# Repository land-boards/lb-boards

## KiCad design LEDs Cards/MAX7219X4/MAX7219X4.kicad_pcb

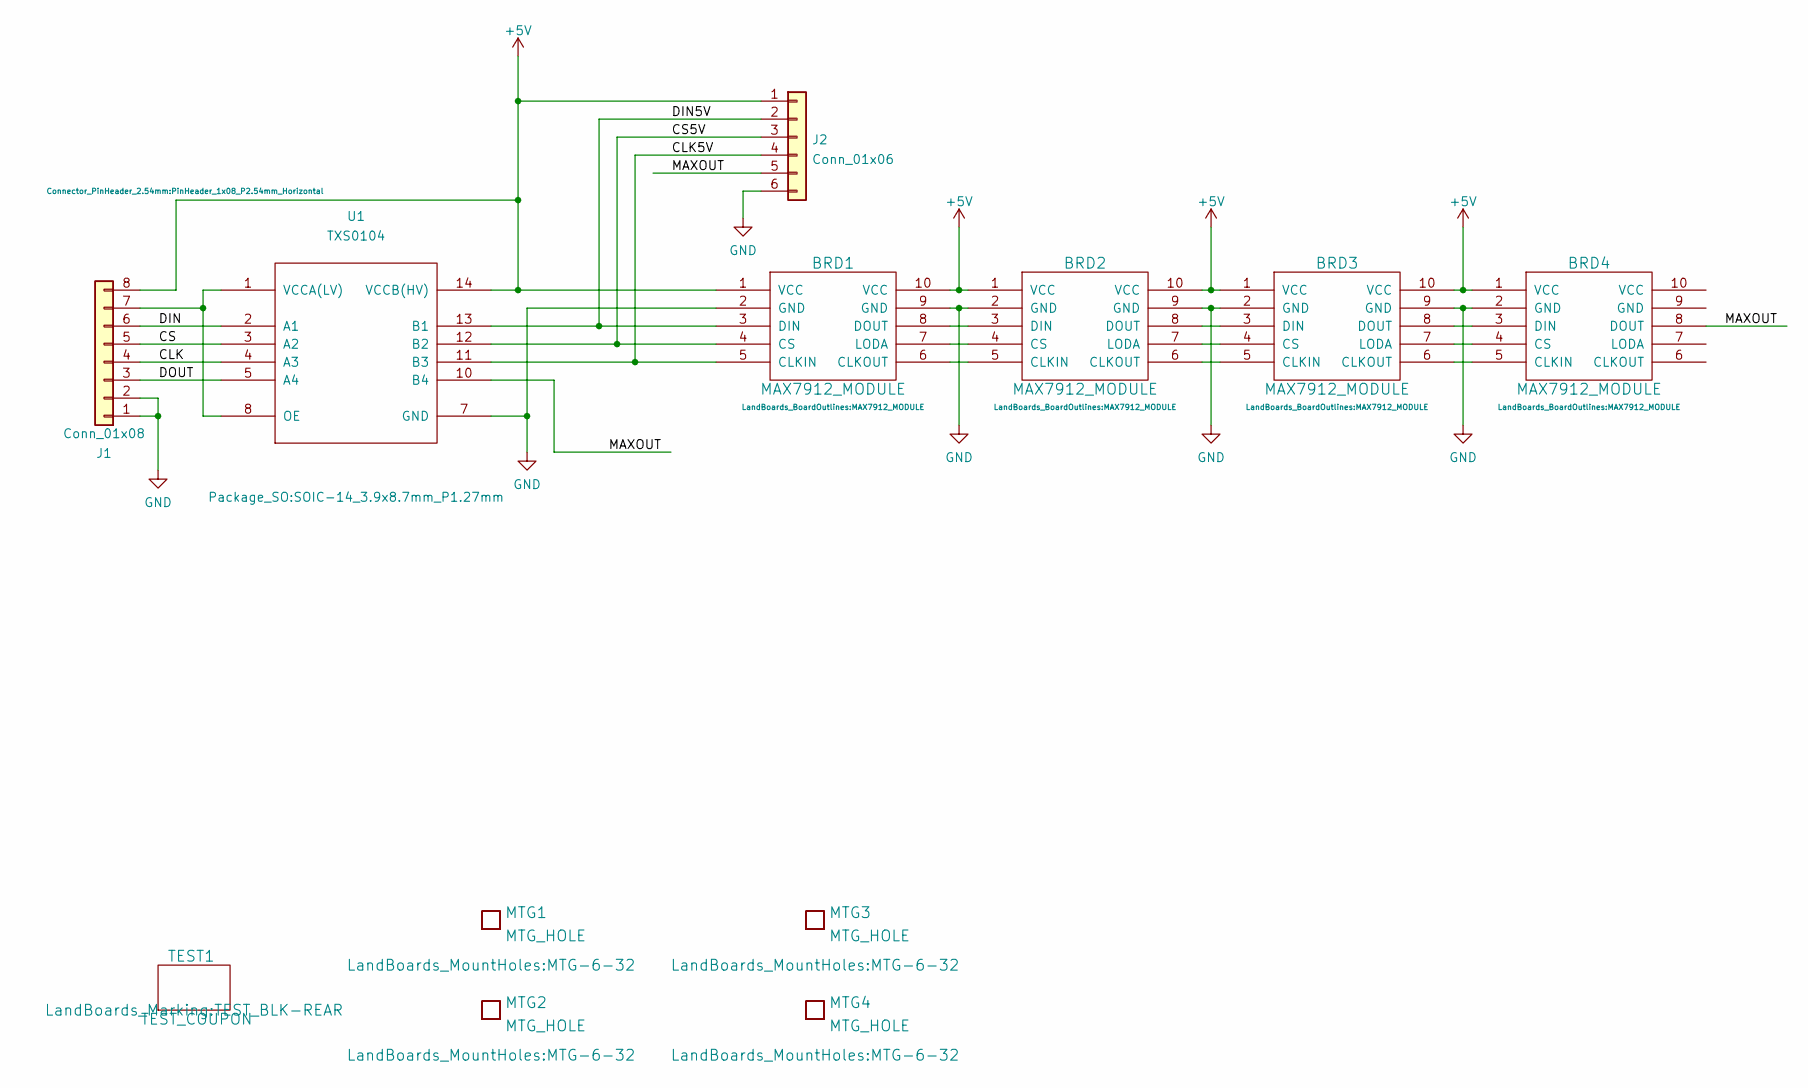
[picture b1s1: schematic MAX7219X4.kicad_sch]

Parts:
BRD1, BRD2, BRD3, BRD4: MAX7912_MODULE
J1: Conn_01x08; PinHeader_1x08_P2.54mm_Horizontal
J2: Conn_01x06; PinHeader_1x06_P2.54mm_Horizontal
MTG1, MTG2, MTG3, MTG4: MTG_HOLE; MTG-6-32
TEST1: TEST_COUPON; TEST_BLK-REAR
U1: TXS0104; SOIC-14_3.9x8.7mm_P1.27mm

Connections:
+5V: BRD1.1 (VCC), BRD1.10 (VCC), BRD2.1 (VCC), BRD2.10 (VCC), BRD3.1 (VCC), BRD3.10 (VCC), BRD4.1 (VCC), J1.8, J2.1, U1.14 (VCCB(HV))
/CLK: J1.4, U1.4 (A3)
/CLK5V: BRD1.5 (CLKIN), J2.4, U1.11 (B3)
/CS: J1.5, U1.3 (A2)
/CS5V: BRD1.4 (CS), J2.3, U1.12 (B2)
/DIN: J1.6, U1.2 (A1)
/DIN5V: BRD1.3 (DIN), J2.2, U1.13 (B1)
/DOUT: J1.3, U1.5 (A4)
/MAXOUT: BRD4.8 (DOUT), J2.5, U1.10 (B4)
GND: BRD1.2 (GND), BRD1.9 (GND), BRD2.2 (GND), BRD2.9 (GND), BRD3.2 (GND), BRD3.9 (GND), BRD4.2 (GND), J1.1, J1.2, J2.6, U1.7 (GND)
unnamed: BRD1.6 (CLKOUT), BRD2.5 (CLKIN)
unnamed: BRD1.7 (LODA), BRD2.4 (CS)
unnamed: BRD1.8 (DOUT), BRD2.3 (DIN)
unnamed: BRD2.6 (CLKOUT), BRD3.5 (CLKIN)
unnamed: BRD2.7 (LODA), BRD3.4 (CS)
unnamed: BRD2.8 (DOUT), BRD3.3 (DIN)
unnamed: BRD3.6 (CLKOUT), BRD4.5 (CLKIN)
unnamed: BRD3.7 (LODA), BRD4.4 (CS)
unnamed: BRD3.8 (DOUT), BRD4.3 (DIN)
unnamed: J1.7, U1.1 (VCCA(LV)), U1.8 (OE)

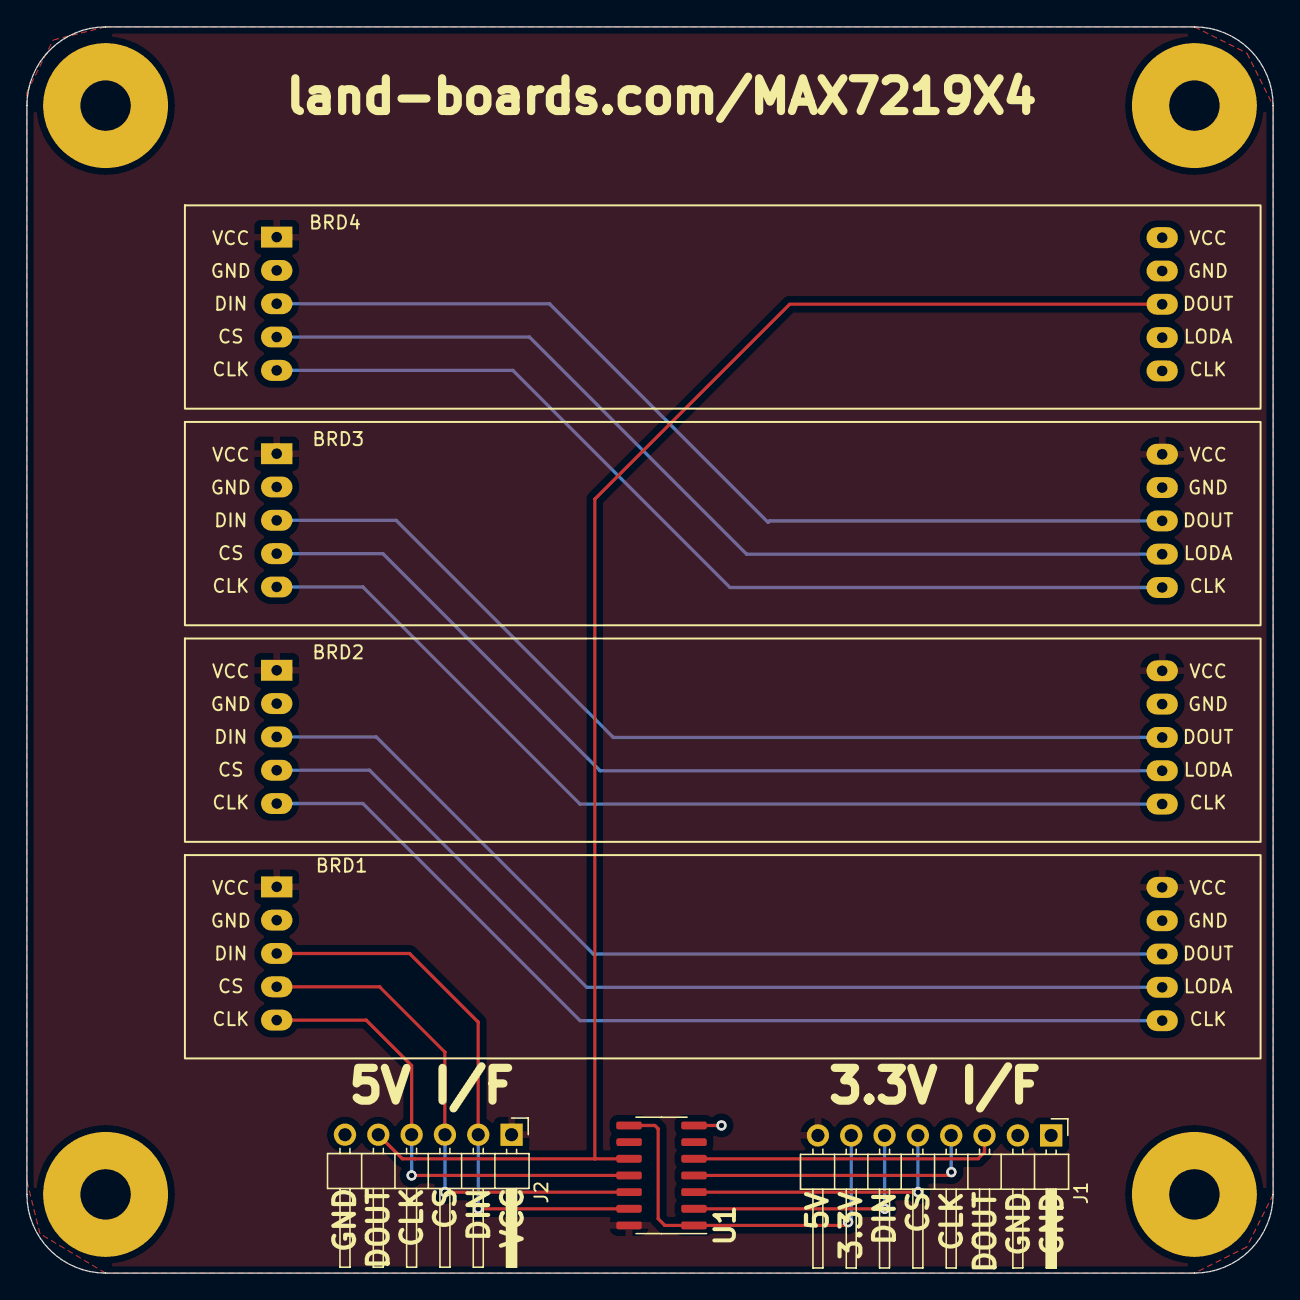
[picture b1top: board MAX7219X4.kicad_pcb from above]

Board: 2 copper layers, 95.0 x 95.0 mm, 12 parts (0 on the bottom side), 20 nets.

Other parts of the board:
TEST: TEST_COUPON; TEST_BLK-REAR

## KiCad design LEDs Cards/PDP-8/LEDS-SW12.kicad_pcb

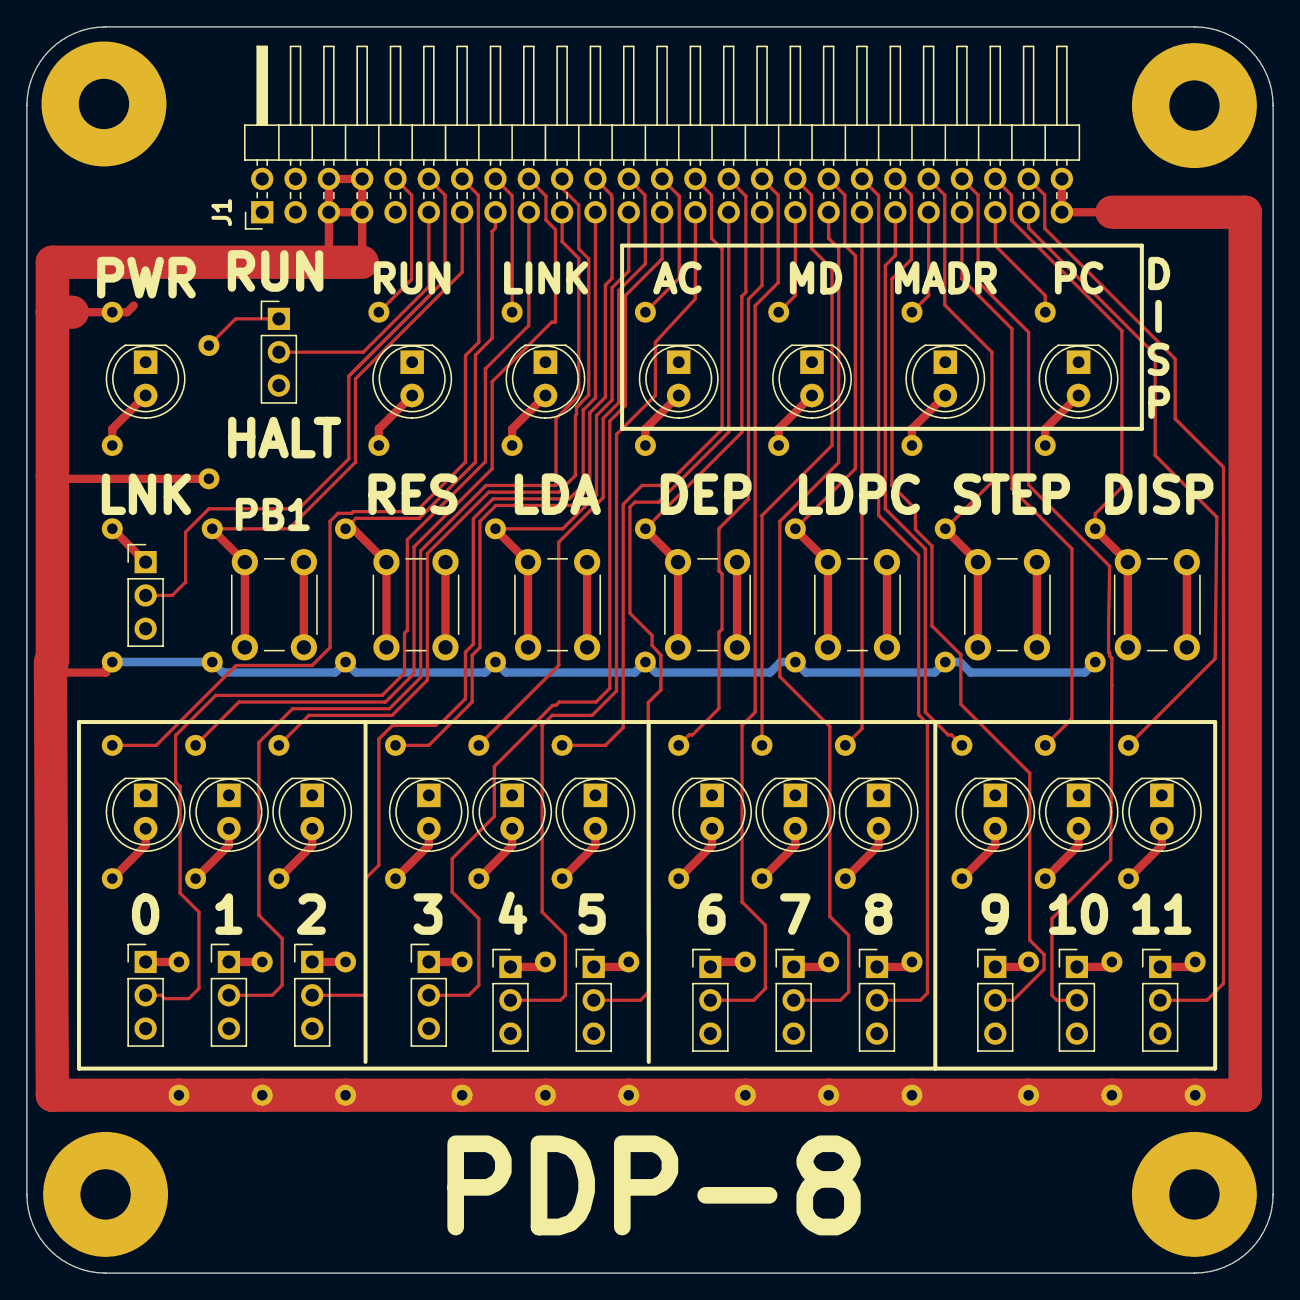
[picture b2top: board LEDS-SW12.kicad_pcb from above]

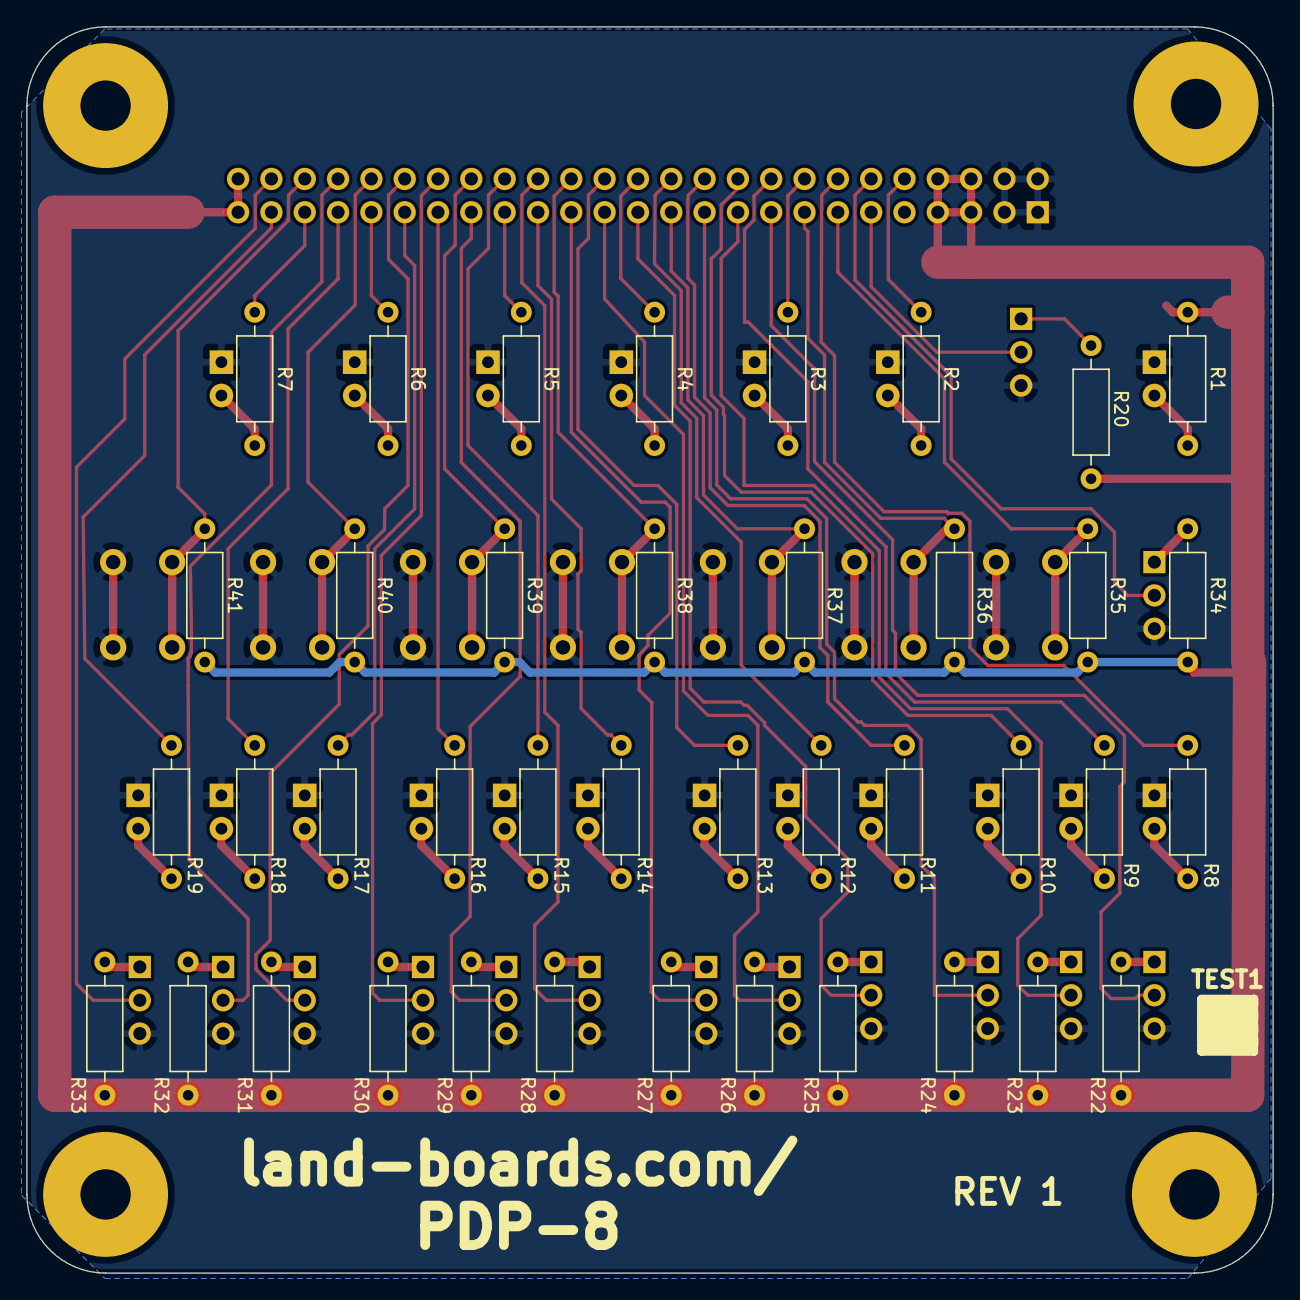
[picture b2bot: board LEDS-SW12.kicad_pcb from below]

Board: 2 copper layers, 95.0 x 95.0 mm, 86 parts (40 on the bottom side), 74 nets.

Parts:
D1, D2, D3, D4, D5, D6, D7, D8, D9, D10, D11, D12, D13, D14, D15, D16, D17, D18, D19: LED-fixed; LED_D5.0mm
J1: Conn_02x25_Odd_Even; PinHeader_2x25_P2.54mm_Horizontal
MTG1, MTG2, MTG3: MTG_HOLE; MTG-6-32
MTG?1: MTG_HOLE; MTG-6-32
R1, R2, R3, R4, R5, R6, R7, R8, R9, R10, R11, R12, R13, R14, R15, R16, R17, R18, R19: 560; R_Axial_DIN0207_L6.3mm_D2.5mm_P10.16mm_Horizontal
R20, R22, R23, R24, R25, R26, R27, R28, R29, R30, R31, R32, R33, R34, R35, R36, R37, R38, R39, R40, R41: 10K; R_Axial_DIN0207_L6.3mm_D2.5mm_P10.16mm_Horizontal
SW1, SW2, SW3, SW4, SW5, SW6, SW7, SW8, SW9, SW10, SW11, SW12, SW13, SW14: SW_SPDT; PinHeader_1x03_P2.54mm_Vertical
SW15, SW16, SW17, SW18, SW19, SW20, SW21: SW_Push; SW_PUSH_6mm_H8.5mm
TEST1: COUPON; TEST_BLK-REAR

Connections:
+5V: J1.5, J1.6, J1.7, J1.8, J1.49, J1.50, R1.2, R20.1, R22.1, R23.1, R24.1, R25.1, R26.1, R27.1, R28.1, R29.1, R30.1, R31.1, R32.1, R33.1, R34.1, R35.1, R36.1, R37.1, R38.1, R39.1, R40.1, R41.1
/DEPOSIT: J1.30, R38.2, SW18.2
/DISP: J1.46, R41.2, SW21.2
/DISPACC: J1.26, R4.2
/DISPMADR: J1.41, R6.2
/DISPMBUF: J1.33, R5.2
/DISPPC: J1.45, R7.2
/DS0: J1.14, R8.2
/DS1: J1.18, R9.2
/DS2: J1.20, R10.2
/DS3: J1.22, R11.2
/DS4: J1.24, R12.2
/DS5: J1.28, R13.2
/DS6: J1.31, R14.2
/DS7: J1.34, R15.2
/DS8: J1.37, R16.2
/DS9: J1.39, R17.2
/DS10: J1.43, R18.2
/DS11: J1.47, R19.2
/LDPC: J1.36, R39.2, SW19.2
/LINK: J1.12, SW2.2
/LINKLED: J1.16, R3.2
/LOADACC: J1.23, R37.2, SW17.2
/PB1: J1.13, R35.2, SW15.2
/RESET: J1.15, R36.2, SW16.2
/RUN: J1.11, SW1.2
/RUNLED: J1.10, R2.2
/SS0: J1.17, SW3.2
/SS1: J1.19, SW4.2
/SS2: J1.21, SW5.2
/SS3: J1.25, SW6.2
/SS4: J1.27, SW7.2
/SS5: J1.29, SW8.2
/SS6: J1.32, SW9.2
/SS7: J1.35, SW10.2
/SS8: J1.38, SW11.2
/SS9: J1.40, SW12.2
/SS10: J1.44, SW13.2
/SS11: J1.48, SW14.2
/STEP: J1.42, R40.2, SW20.2
GND: D1.1, D2.1, D3.1, D4.1, D5.1, D6.1, D7.1, D8.1, D9.1, D10.1, D11.1, D12.1, D13.1, D14.1, D15.1, D16.1, D17.1, D18.1, D19.1, J1.1, J1.2, J1.3, J1.4, SW1.3, SW2.3, SW3.3, SW4.3, SW5.3, SW6.3, SW7.3, SW8.3, SW9.3, SW10.3, SW11.3, SW12.3, SW13.3, SW14.3, SW15.1, SW16.1, SW17.1, SW18.1, SW19.1, SW20.1, SW21.1
unnamed: D1.2, R1.1
unnamed: D2.2, R2.1
unnamed: D3.2, R3.1
unnamed: D4.2, R4.1
unnamed: D5.2, R5.1
unnamed: D6.2, R6.1
unnamed: D7.2, R7.1
unnamed: D8.2, R8.1
unnamed: D9.2, R9.1
unnamed: D10.2, R10.1
unnamed: D11.2, R11.1
unnamed: D12.2, R12.1
unnamed: D13.2, R13.1
unnamed: D14.2, R14.1
unnamed: D15.2, R15.1
unnamed: D16.2, R16.1
unnamed: D17.2, R17.1
unnamed: D18.2, R18.1
unnamed: D19.2, R19.1
unnamed: R20.2, SW1.1
unnamed: R22.2, SW3.1
unnamed: R23.2, SW4.1
unnamed: R24.2, SW5.1
unnamed: R25.2, SW6.1
unnamed: R26.2, SW7.1
unnamed: R27.2, SW8.1
unnamed: R28.2, SW9.1
unnamed: R29.2, SW10.1
unnamed: R30.2, SW11.1
unnamed: R31.2, SW12.1
unnamed: R32.2, SW13.1
unnamed: R33.2, SW14.1
unnamed: R34.2, SW2.1

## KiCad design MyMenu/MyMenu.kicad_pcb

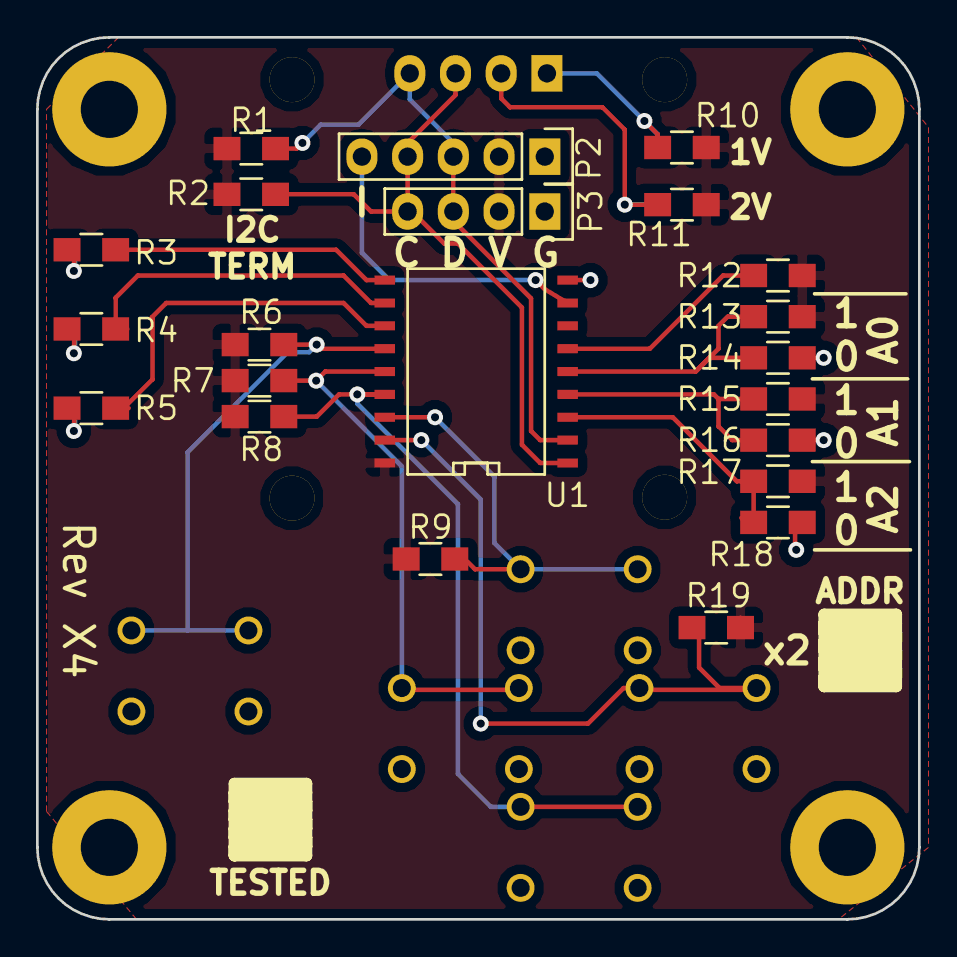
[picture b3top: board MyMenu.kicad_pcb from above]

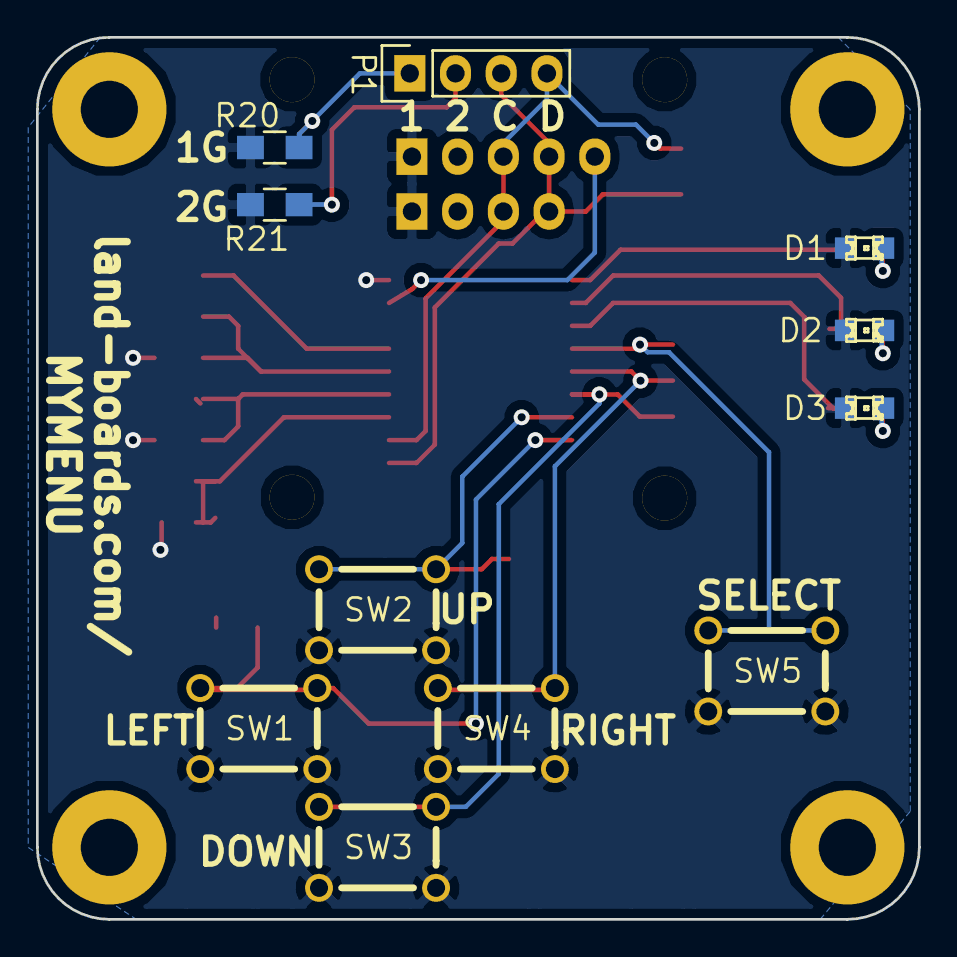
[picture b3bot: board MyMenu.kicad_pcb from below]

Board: 2 copper layers, 49.0 x 49.0 mm, 43 parts (13 on the bottom side), 22 nets.

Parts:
ADDR: VAL**; TEST_BLK-REAR
D1, D2, D3: LED; LED-0805
MTG1, MTG2, MTG3, MTG4: CONN_1; MTG-4-40
MTG5, MTG6, MTG7, MTG8: CONN_1; MTG-2.5MM
P1, P3: CONN_4; Pin_Header_Straight_1x04
P2: CONN_5; Pin_Header_Straight_1x05
R1, R2: 2.2K; R_0805_HandSoldering
R3, R4, R5: 330; R_0805_HandSoldering
R6, R7, R8, R9, R12, R19: 10K; R_0805_HandSoldering
R10, R11, R20, R21: 0/OP; R_0805_HandSoldering
R13, R15, R17: OPEN; R_0805_HandSoldering
R14, R16, R18: 0; R_0805_HandSoldering
SW1, SW2, SW3, SW4, SW5: SW_PUSH_OMRON; SW-PB-6MM
TESTED: VAL**; TEST_BLK-REAR
U1: MCP23008SO; SO18W

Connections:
/A0: R13.2, R14.1, U1.5
/A1: R15.2, R16.1, U1.4
/A2: R17.2, R18.1, U1.3
/GND: D1.2, D2.2, D3.2, P2.1, P3.1, R14.2, R16.2, R18.2, R20.2, R21.2, SW1.3, SW1.4, SW2.3, SW2.4, SW3.3, SW3.4, SW4.3, SW4.4, SW5.3, SW5.4, U1.9
/SCL: P1.3, P2.4, P3.4, R2.2, U1.1
/SDA: P1.4, P2.3, P3.3, R1.2, U1.2
/VCC: P2.2, P3.2, R1.1, R2.1, R6.1, R7.1, R8.1, R9.1, R10.1, R11.1, R12.1, R13.1, R15.1, R17.1, R19.1, U1.18
unnamed: D1.1, R3.2
unnamed: D2.1, R4.2
unnamed: D3.1, R5.2
unnamed: P1.1, R10.2, R20.1
unnamed: P1.2, R11.2, R21.1
unnamed: P2.5, U1.8
unnamed: R3.1, U1.10
unnamed: R4.1, U1.11
unnamed: R5.1, U1.12
unnamed: R6.2, SW5.1, SW5.2, U1.13
unnamed: R7.2, SW4.1, SW4.2, U1.14
unnamed: R8.2, SW3.1, SW3.2, U1.15
unnamed: R9.2, SW2.1, SW2.2, U1.16
unnamed: R12.2, U1.6
unnamed: R19.2, SW1.1, SW1.2, U1.17

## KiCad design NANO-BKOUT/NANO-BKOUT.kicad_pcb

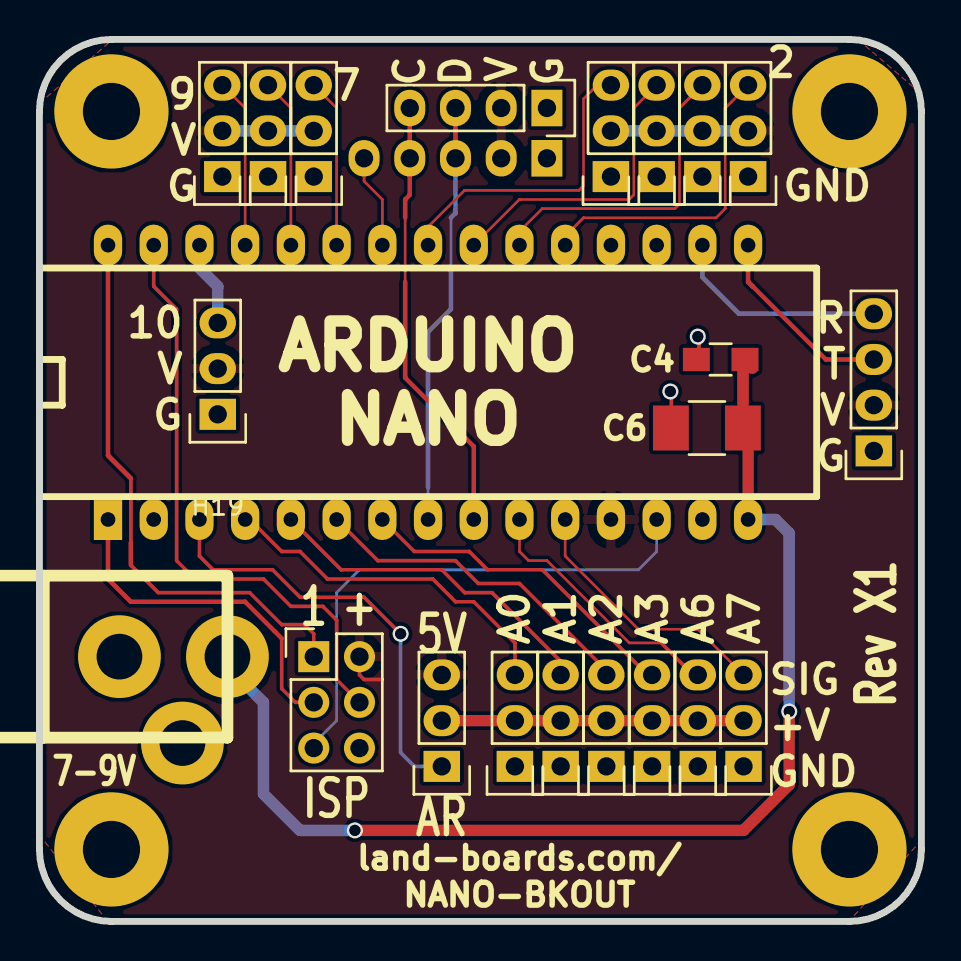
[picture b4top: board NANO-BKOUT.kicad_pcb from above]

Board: 2 copper layers, 49.0 x 49.0 mm, 27 parts (1 on the bottom side), 28 nets.

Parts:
C4: 0.1uF; R_0805_HandSoldering
C6: 22uF; R_1210_HandSoldering
H1, H2, H3, H4, H5, H6, H9, H10, H11, H12, H14, H15, H16, H18, H19: CONN_01X03; Pin_Header_Straight_1x03
H7: CONN_01X05; Pin_Header_Straight_1x05
H8: CONN_02X03; Pin_Header_Straight_2x03
H13, H17: CONN_01X04; Pin_Header_Straight_1x04
J1: DCJ0202; DCJ-NEW
MTG1, MTG2, MTG3, MTG4: CONN_1; MTG-4-40
U5: arduino_nano; arduino_mini

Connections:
+5V: H7.2, H8.2, H9.2, H10.2, H11.2, H12.2, H13.2, H14.2, H15.2, H16.2, H17.2, H18.3, H19.2, U5.12
+9V: C4.1, C6.1, J1.1, U5.15
/A0: H1.3, U5.4
/A1: H2.3, U5.5
/A2: H3.3, U5.6
/A3: H4.3, U5.7
/A6: H5.3, U5.10
/A7: H6.3, U5.11
/AREF: H18.1, U5.3
/D0: H17.3, U5.16
/D1: H17.4, U5.17
/D2: H16.3, U5.20
/D3: H15.3, U5.21
/D4: H14.3, U5.22
/D5: H12.3, U5.23
/D6: H7.5, U5.24
/D7: H11.3, U5.25
/D8: H10.3, U5.26
/D9: H9.3, U5.27
/D10: H19.3, U5.28
/D11: H8.4, U5.29
/D12: H8.1, U5.30
/D13: H8.3, U5.1
/SCL: H7.4, H13.4, U5.9
/SDA: H7.3, H13.3, U5.8
/~RST: H8.5, U5.13
GND: C4.2, C6.2, H1.1, H2.1, H3.1, H4.1, H5.1, H6.1, H7.1, H8.6, H9.1, H10.1, H11.1, H12.1, H13.1, H14.1, H15.1, H16.1, H17.1, H19.1, J1.2, J1.3, U5.14, U5.19
unnamed: H1.2, H2.2, H3.2, H4.2, H5.2, H6.2, H18.2

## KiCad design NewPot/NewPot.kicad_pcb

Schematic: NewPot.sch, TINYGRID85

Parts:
C1, C2: 0.1uF; C_0805_HandSoldering
H2: CONN_02X04; Pin_Header_Straight_2x04
R1, R2, R3: 10K; R_0805_HandSoldering
SW1: ROTARY-ENC; ROT-ENC-12MM
U1: ATTINY85; SOIC-8_3.9x4.9mm_Pitch1.27mm

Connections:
/D0: H2.4, R3.2, SW1.A, U1.5 (D0)
/D1: H2.1, R2.2, SW1.B, U1.6 (D1)
/D2: H2.3, U1.7 (D(A)2)
/D3: H2.7, U1.2 (D(A)3)
/D4: H2.8, U1.3 (D(A)4)
/RST*: C1.1, H2.5, R1.2, SW1.S1, U1.1 (RES*)
GND: C1.2, C2.2, H2.6, SW1.C, SW1.S2, U1.4 (GND)
VCC: C2.1, H2.2, R1.1, R2.1, R3.1, U1.8 (VCC)

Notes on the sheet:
MICROPROCESSOR

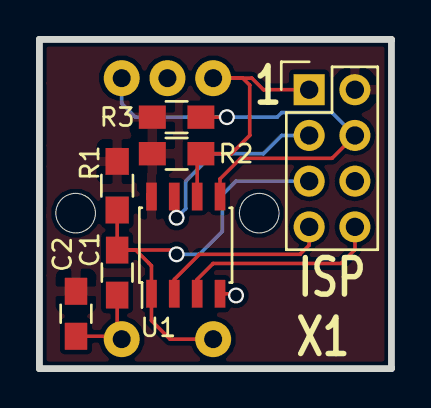
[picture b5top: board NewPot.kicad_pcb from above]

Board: 2 copper layers, 19.6 x 18.3 mm, 8 parts (1 on the bottom side), 8 nets.

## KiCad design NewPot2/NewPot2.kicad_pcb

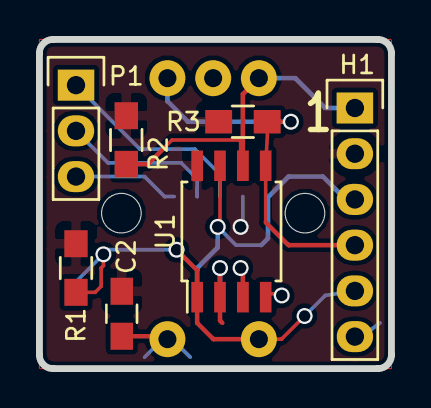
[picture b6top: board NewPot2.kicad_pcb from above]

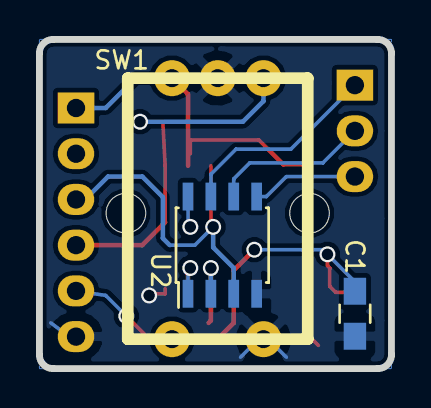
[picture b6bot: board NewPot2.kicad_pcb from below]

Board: 2 copper layers, 19.6 x 18.3 mm, 10 parts (3 on the bottom side), 11 nets.

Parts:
C1, C2: 0.1uF; C_0805_HandSoldering
H1: CONN_02X03; Pin_Header_Straight_1x06
P1: CONN_01X03; Pin_Header_Straight_1x03
R1, R2, R3: 10K; R_0805_HandSoldering
SW1: ROTARY-ENC; ROT-ENC-12MM
U1: ATTINY85; SOIJ-8_5.3x5.3mm_Pitch1.27mm
U2: MCP41X1; SOIC-8_3.9x4.9mm_Pitch1.27mm

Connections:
/D0: H1.4, R3.2, SW1.A, U1.5
/D1: H1.1, R2.2, SW1.B, U1.6
/D2: H1.3, U1.7, U2.3
/D3: U1.2, U2.2
/D4: U1.3, U2.1
/RST*: C1.1, H1.5, R1.2, SW1.S1, U1.1
GND: C1.2, C2.2, H1.6, SW1.C, SW1.S2, U1.4, U2.4
unnamed: P1.1, U2.7
unnamed: P1.2, U2.6
unnamed: P1.3, U2.5
VCC: C2.1, H1.2, R1.1, R2.1, R3.1, U1.8, U2.8
